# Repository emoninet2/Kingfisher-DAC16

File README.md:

# Kingfisher-DAC16
A 16 channel. 16-bit DAC board.

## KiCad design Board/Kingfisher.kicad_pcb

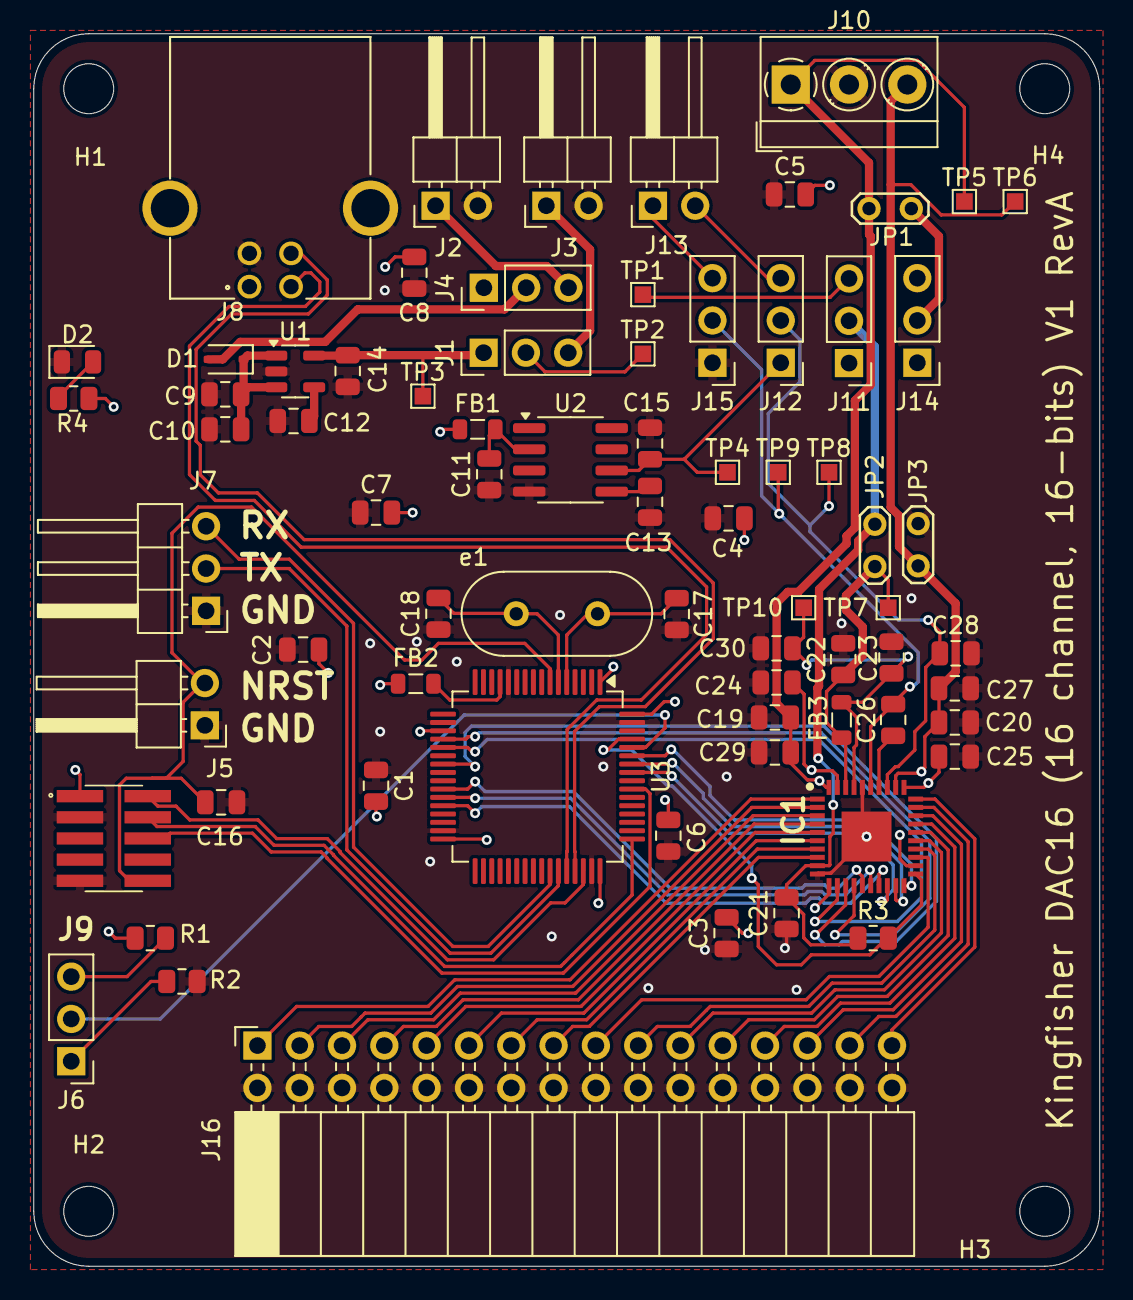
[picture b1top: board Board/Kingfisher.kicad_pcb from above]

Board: 4 copper layers, 64.0 x 74.0 mm, 77 parts (0 on the bottom side), 64 nets.

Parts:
C1, C2, C12: 10nF; C_0805_2012Metric
C3, C4, C5, C6, C10, C16, C19, C20, C21, C22, C23, C24, C25: 100nF; C_0805_2012Metric
C7, C9, C11, C13, C14, C30: 1uF; C_0805_2012Metric
C8, C15, C27, C29: 10uF; C_0805_2012Metric
C17, C18: 30pF; C_0805_2012Metric
C26: 330pF; C_0805_2012Metric
C28: 150nF; C_0805_2012Metric
D1: BAT60AE6327HTSA1; D_SOD-323
D2: LED; LED_0805_2012Metric
FB1, FB2, FB3: HZ0805E601R-10; L_0805_2012Metric
H1, H2, H3, H4: MountingHole; MountingHole_3mm
IC1: DAC81416RHAT; QFN50P600X600X100-41N-D
J1: SEL 3V3; PinHeader_1x03_P2.54mm_Vertical
J2: 5V EXT; PinHeader_1x02_P2.54mm_Horizontal
J3: 3V3 EXT; PinHeader_1x02_P2.54mm_Horizontal
J4: SEL 5V; PinHeader_1x03_P2.54mm_Vertical
J5: Conn_01x02_Male; PinHeader_1x02_P2.54mm_Horizontal
J6: Conn_01x03_Male; PinHeader_1x03_P2.54mm_Vertical
J7: UART; PinHeader_1x03_P2.54mm_Horizontal
J8: 292304-1; TE_292304-1
J9: FTSH-105-01-F-DV-K-P-TR; FTSH-105-XX-YYY-DV-K-P-TR
J10: Screw_Terminal_01x03; TerminalBlock_MetzConnect_Type059_RT06303HBWC_1x03_P3.50mm_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
J11, J14: DAC_VDD_SEL; PinHeader_1x03_P2.54mm_Vertical
J12, J15: DAC_REF_SEL; PinHeader_1x03_P2.54mm_Vertical
J13: DAC_EXT_REF; PinHeader_1x02_P2.54mm_Horizontal
J16: Conn_02x16_Counter_Clockwise; PinSocket_2x16_P2.54mm_Horizontal
JP1, JP2, JP3: Jumper_01x02_2.54mm; TestPoint_2Pads_Pitch2.54mm_Drill0.8mm
R1, R2, R3: 10K; R_0805_2012Metric
R4: 100; R_0805_2012Metric
TP1, TP2, TP3, TP4, TP5, TP6, TP7, TP8, TP9, TP10: TestPoint; TestPoint_Pad_1.0x1.0mm
U1: LDK130M33R; SOT-23-5
U2: REF5025AID; SOIC-8_3.9x4.9mm_P1.27mm
U3: STM32L476RGT6; LQFP-64_10x10mm_P0.5mm
e1: ECS-160-20-4X; Crystal_HC49-4H_Vertical

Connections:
3.3V_EXT: J1.3, J3.1
3.3V_REG: C14.2, J1.1, TP3.1, U1.5 (VOUT)
5V_EXT: J2.1, J4.3
+3V3: C1.2, C2.2, C3.2, C4.2, C5.2, C6.2, C7.2, C8.2, FB1.1, FB2.1, J1.2, J9.1, J11.1, J14.1, R1.1, R4.2, TP2.1, U3.1 (VBAT), U3.19 (VDD), U3.32 (VDD), U3.48 (VDDUSB), U3.64 (VDD)
+5V: D1.2 (A), J4.2, J11.3, J14.3, TP1.1
BOOT0: J6.2, U3.60 (PH3)
DAC_GNDREF: C26.1, IC1.35 (REFGND), J15.2, TP9.1
DAC_OUT_0: IC1.1 (OUT0), J16.1
DAC_OUT_1: IC1.2 (OUT1), J16.3
DAC_OUT_2: IC1.3 (OUT2), J16.5
DAC_OUT_3: IC1.4 (OUT3), J16.7
DAC_OUT_4: IC1.5 (OUT4), J16.9
DAC_OUT_5: IC1.6 (OUT5), J16.11
DAC_OUT_6: IC1.7 (OUT6), J16.13
DAC_OUT_7: IC1.8 (OUT7), J16.15
DAC_OUT_8: IC1.23 (OUT8), J16.17
DAC_OUT_9: IC1.24 (OUT9), J16.19
DAC_OUT_10: IC1.25 (OUT10), J16.21
DAC_OUT_11: IC1.26 (OUT11), J16.23
DAC_OUT_12: IC1.27 (OUT12), J16.25
DAC_OUT_13: IC1.28 (OUT13), J16.27
DAC_OUT_14: IC1.29 (OUT14), J16.29
DAC_OUT_15: IC1.30 (OUT15), J16.31
DAC_REF: C28.1, IC1.33 (REF), J12.2, TP8.1
DAC_SCLK: IC1.12 (SCLK), U3.21 (PA5)
DAC_SDI: IC1.13 (SDI), U3.23 (PA7)
DAC_TOGGLE0: IC1.15 (TOGGLE0), U3.26 (PB0)
DAC_TOGGLE1: IC1.16 (TOGGLE1), U3.27 (PB1)
DAC_TOGGLE2: IC1.17 (TOGGLE2), U3.28 (PB2)
DAC_VAA: C23.2, C30.2, FB3.2, IC1.37 (VAA), TP10.1
DAC_VCC: C19.2, C25.2, C29.2, IC1.31 (VCC_1), IC1.40 (VCC_2), J10.1, JP1.1 (A), TP5.1
DAC_VDD: C22.2, FB3.1, IC1.38 (VDD), JP2.2 (B), TP7.1
DAC_VIO: C21.2, IC1.9 (VIO), J11.2, JP2.1 (A), R3.1
DAC_VSS: C20.2, C24.2, C27.2, IC1.32 (VSS_1), IC1.39 (VSS_2), J10.3, JP3.1 (A), TP6.1
DAC_nALMOUT: IC1.21 (~ALMOUT), R3.2, U3.61 (PB8)
DAC_nCLR: IC1.20 (~CLR), U3.59 (PB7)
DAC_nCS: IC1.14 (~CS), U3.20 (PA4)
DAC_nLDAC: IC1.18 (~LDAC), U3.57 (PB5)
DAC_nRESET: IC1.19 (~RESET), U3.58 (PB6)
EXT_REF_2V5: J12.3, J13.2
GND: C1.1, C2.1, C3.1, C4.1, C5.1, C6.1, C7.1, C8.1, C9.1, C10.1, C11.1, C12.1, C13.1, C14.1, C15.1, C16.1, C17.1, C18.1, C19.1, C20.1, C21.1, C22.1, C23.1, C24.1, C25.1, C27.1, C28.2, C29.1, C30.1, D2.1 (K), IC1.10 (GND_1), IC1.36 (GND_2), IC1.41 (EPAD), J2.2, J3.2, J5.1, J7.1, J8.0 (SHEILD), J8.4 (GND), J9.3, J9.9, J10.2, J15.1, J16.2, J16.4, J16.6, J16.8, J16.10, J16.12, J16.14, J16.16, J16.18, J16.20, J16.22, J16.24, J16.26, J16.28, J16.30, J16.32, JP3.2 (B), R2.2, U1.2 (GND), U2.4 (GND), U3.12 (VSSA), U3.18 (VSS), U3.31 (VSS), U3.47 (VSS), U3.63 (VSS)
JTCK_SWCLK: J9.4, U3.49 (PA14)
JTDO_SWO: J9.6, U3.55 (PB3)
JTMS_SWDIO: J9.2, U3.46 (PA13)
NRST: C16.2, J5.2, J9.10, U3.7 (NRST)
unnamed: C9.2, C10.2, D1.1 (K), U1.1 (VIN), U1.3 (INH)
unnamed: D2.2 (A), R4.1
unnamed: C26.2, IC1.34 (REFCMP)
unnamed: J6.1, R2.1
unnamed: J6.3, R1.2
unnamed: J13.1, J15.3
unnamed: J14.2, JP1.2 (B)
unnamed: C12.2, U1.4 (BYP)
unnamed: C13.2, U2.5 (Trim/NR)
unnamed: C11.2, FB1.2, U2.2 (Vin)
unnamed: C17.2, U3.5 (PH0), e1.1
unnamed: C18.2, U3.6 (PH1), e1.2
unnamed: FB2.2, U3.13 (VDDA)
REF_2V5: C15.2, J12.1, TP4.1, U2.6 (Vout)
UART_RX: J7.3, U3.42 (PA9)
UART_TX: J7.2, U3.43 (PA10)
USB_OTG_FS_D+: J8.3 (D+), U3.45 (PA12)
USB_OTG_FS_D-: J8.2 (D-), U3.44 (PA11)
USB_VBUS: J4.1, J8.1 (VBUS)

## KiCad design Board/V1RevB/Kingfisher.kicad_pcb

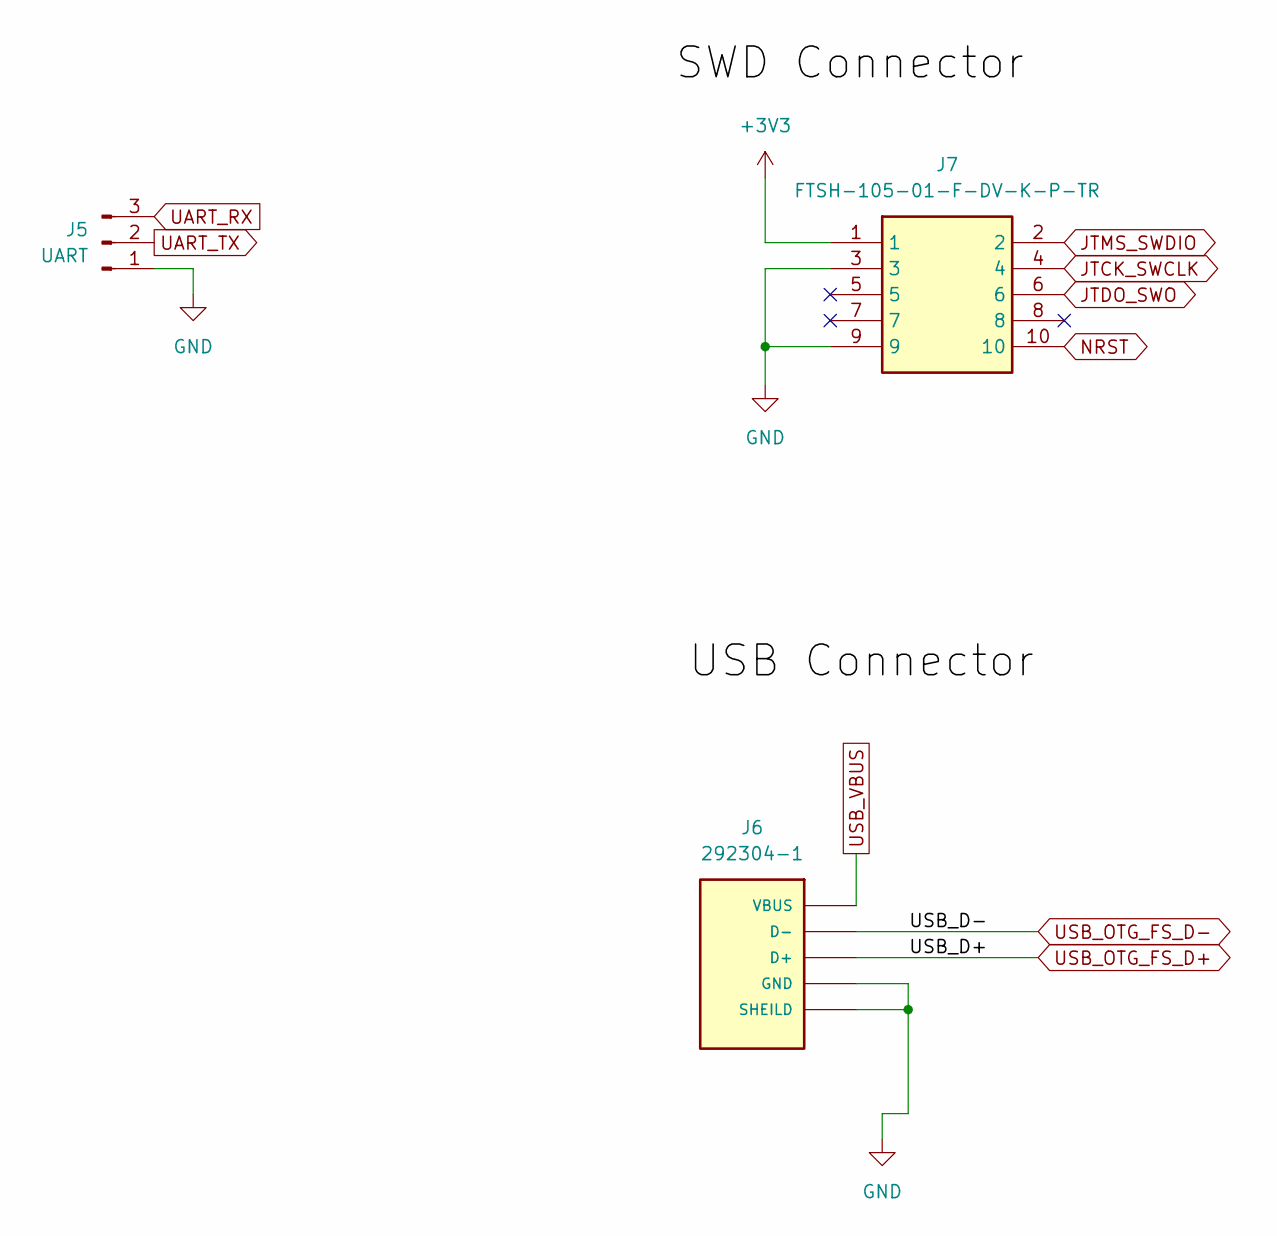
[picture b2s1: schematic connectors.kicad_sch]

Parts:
J5: UART; PinHeader_1x03_P2.54mm_Horizontal; Manufacturer_Part_Number TSW-103-14-TM-S; Farnell 1593427
J6: 292304-1; TE_292304-1; Manufacturer_Part_Number 292304-1; LCSC C86462
J7: FTSH-105-01-F-DV-K-P-TR; FTSH-105-XX-YYY-DV-K-P-TR; Mouser Part Number FTSH-105-01-F-DV-K-P-TR

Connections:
+3V3: J7.1; also elsewhere on the board
GND: J5.1, J6.0 (SHEILD), J6.4 (GND), J7.3, J7.9; also elsewhere on the board
JTCK_SWCLK: J7.4; also elsewhere on the board
JTDO_SWO: J7.6; also elsewhere on the board
JTMS_SWDIO: J7.2; also elsewhere on the board
NRST: J7.10; also elsewhere on the board
UART_RX: J5.3; also elsewhere on the board
UART_TX: J5.2; also elsewhere on the board
USB_OTG_FS_D+: J6.3 (D+); also elsewhere on the board
USB_OTG_FS_D-: J6.2 (D-); also elsewhere on the board
USB_VBUS: J6.1 (VBUS); also elsewhere on the board

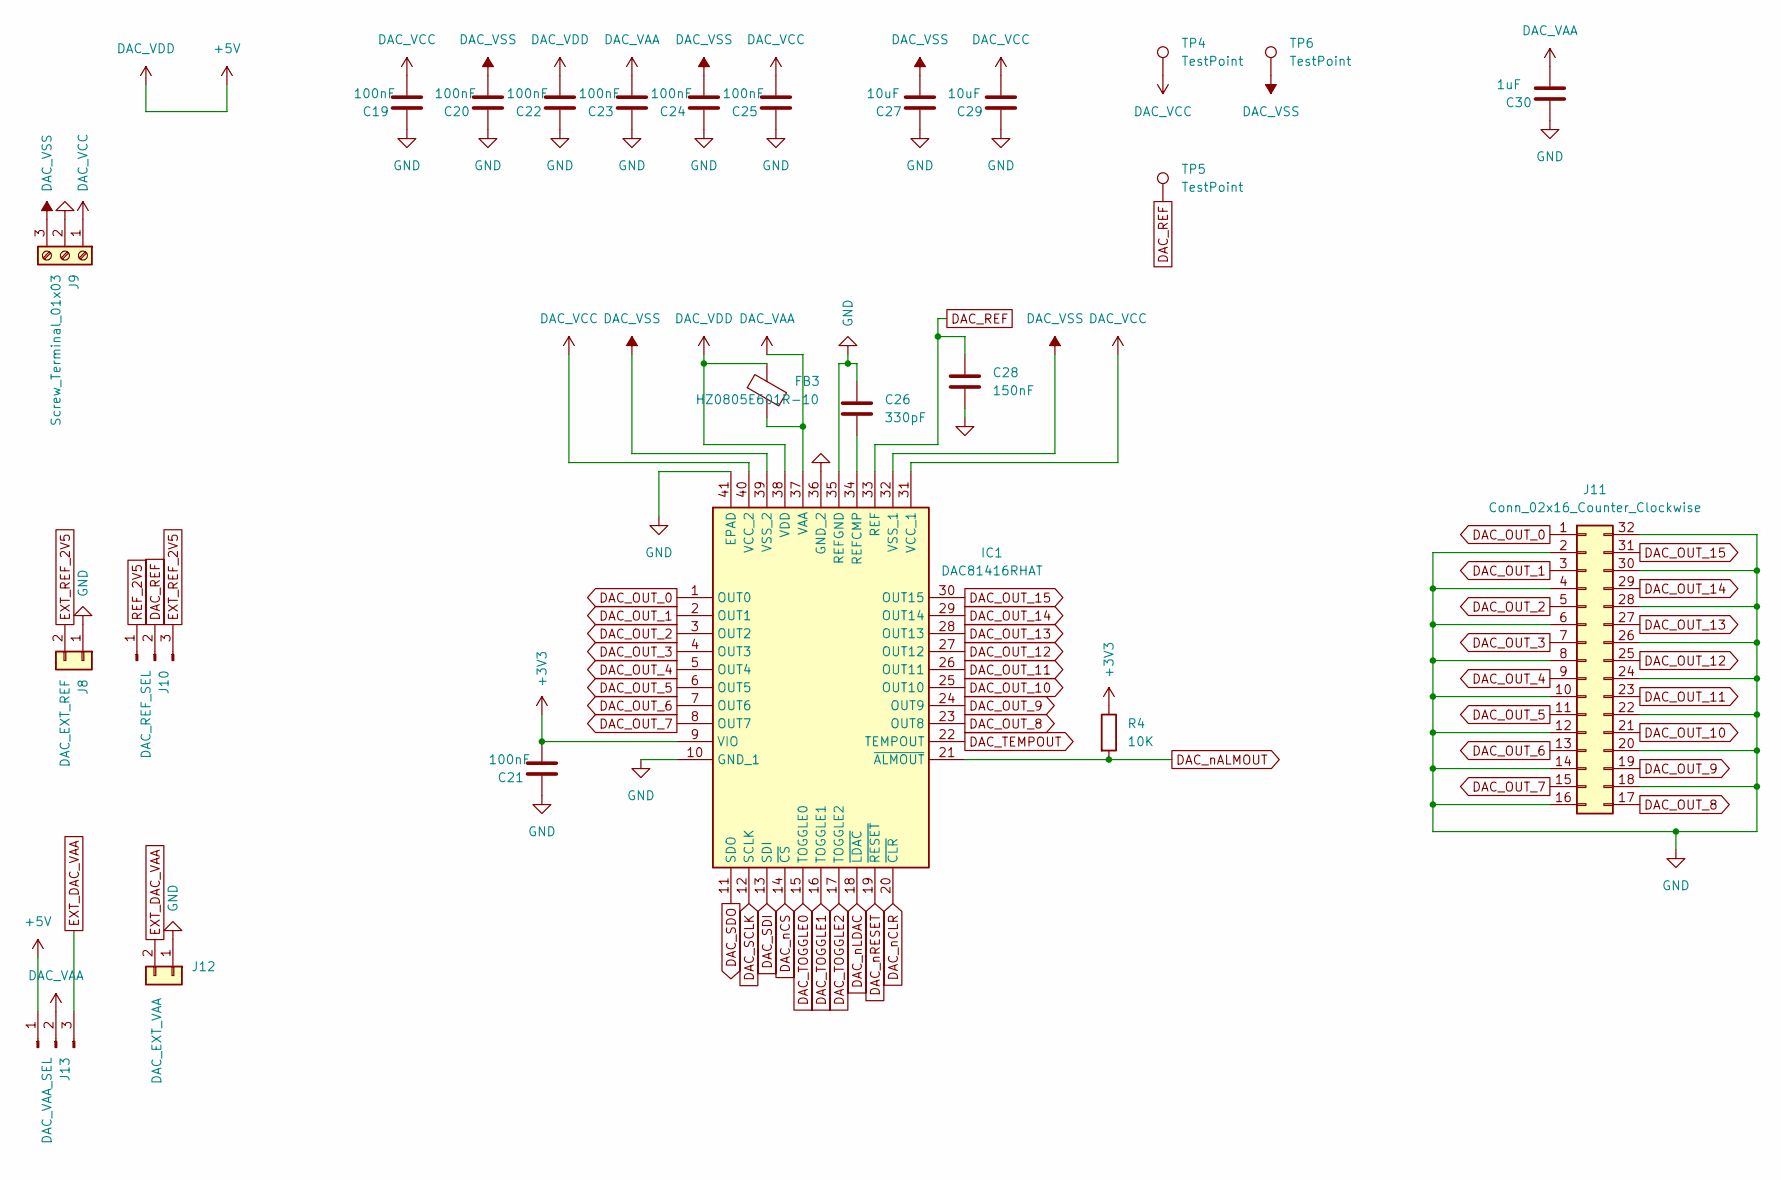
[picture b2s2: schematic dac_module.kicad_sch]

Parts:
C19, C20, C21, C22, C23, C24, C25: 100nF; C_0805_2012Metric; Manufacturer_Part_Number CL21B104KBCNNNC; LCSC C1711
C26: 330pF; C_0805_2012Metric; Mouser Part Number 08052C331KAT2A; Digi-Key Part Number 478-KGM21NR72D331KTCT-ND
C27, C29: 10uF; C_0805_2012Metric; Manufacturer_Part_Number CL21A106KOQNNNG; LCSC C307520
C28: 150nF; C_0805_2012Metric; Mouser Part Number C0805C154K5RACAUTO; Digi-Key Part Number 399-15888-1-ND
C30: 1uF; C_0805_2012Metric; Manufacturer_Part_Number CL21A105KBCLNNC; LCSC C318694
FB3: HZ0805E601R-10; L_0805_2012Metric; Manufacturer_Part_Number HZ0805E601R-10; Digi-Key Part Number 240-2399-1-ND
IC1: DAC81416RHAT; QFN50P600X600X100-41N-D; Mouser Part Number DAC81416RHAT
J8: DAC_EXT_REF; PinHeader_1x02_P2.54mm_Horizontal; Mouser Part Number MC34745; Farnell 1593426
J9: Screw_Terminal_01x03; TerminalBlock_MetzConnect_Type059_RT06303HBWC_1x03_P3.50mm_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; Mouser Part Number METZ CONNECT; Farnell 31059103
J10: DAC_REF_SEL; PinHeader_1x03_P2.54mm_Vertical; Manufacturer_Part_Number TSW-103-14-TM-S; Farnell 3398484
J11: Conn_02x16_Counter_Clockwise; PinSocket_2x16_P2.54mm_Horizontal; Mouser Part Number SSW-108-02-F-D-RA; Farnell 3661253
J12: DAC_EXT_VAA; PinHeader_1x02_P2.54mm_Horizontal; Mouser Part Number MC34745; Farnell 1593426
J13: DAC_VAA_SEL; PinHeader_1x03_P2.54mm_Vertical; Manufacturer_Part_Number TSW-103-14-TM-S; Farnell 3398484
R4: 10K; R_0805_2012Metric; Mouser Part Number CRCW080510K0JNEAIF; Farnell 1739242
TP4, TP5, TP6: TestPoint; TestPoint_Pad_1.0x1.0mm

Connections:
+3V3: C21.2, IC1.9 (VIO), R4.1; also elsewhere on the board
+5V: C22.2, FB3.1, IC1.38 (VDD), J13.1; also elsewhere on the board
DAC_OUT_0: IC1.1 (OUT0), J11.1
DAC_OUT_1: IC1.2 (OUT1), J11.3
DAC_OUT_2: IC1.3 (OUT2), J11.5
DAC_OUT_3: IC1.4 (OUT3), J11.7
DAC_OUT_4: IC1.5 (OUT4), J11.9
DAC_OUT_5: IC1.6 (OUT5), J11.11
DAC_OUT_6: IC1.7 (OUT6), J11.13
DAC_OUT_7: IC1.8 (OUT7), J11.15
DAC_OUT_8: IC1.23 (OUT8), J11.17
DAC_OUT_9: IC1.24 (OUT9), J11.19
DAC_OUT_10: IC1.25 (OUT10), J11.21
DAC_OUT_11: IC1.26 (OUT11), J11.23
DAC_OUT_12: IC1.27 (OUT12), J11.25
DAC_OUT_13: IC1.28 (OUT13), J11.27
DAC_OUT_14: IC1.29 (OUT14), J11.29
DAC_OUT_15: IC1.30 (OUT15), J11.31
DAC_REF: C28.1, IC1.33 (REF), J10.2, TP5.1
DAC_SCLK: IC1.12 (SCLK); also elsewhere on the board
DAC_SDI: IC1.13 (SDI); also elsewhere on the board
DAC_SDO: IC1.11 (SDO); also elsewhere on the board
DAC_TEMPOUT: IC1.22 (TEMPOUT)
DAC_TOGGLE0: IC1.15 (TOGGLE0); also elsewhere on the board
DAC_TOGGLE1: IC1.16 (TOGGLE1); also elsewhere on the board
DAC_TOGGLE2: IC1.17 (TOGGLE2); also elsewhere on the board
DAC_VAA: C23.2, C30.2, FB3.2, IC1.37 (VAA), J13.2
DAC_VCC: C19.2, C25.2, C29.2, IC1.31 (VCC_1), IC1.40 (VCC_2), J9.1, TP4.1
DAC_VSS: C20.2, C24.2, C27.2, IC1.32 (VSS_1), IC1.39 (VSS_2), J9.3, TP6.1
DAC_nALMOUT: IC1.21 (~ALMOUT), R4.2; also elsewhere on the board
DAC_nCLR: IC1.20 (~CLR); also elsewhere on the board
DAC_nCS: IC1.14 (~CS); also elsewhere on the board
DAC_nLDAC: IC1.18 (~LDAC); also elsewhere on the board
DAC_nRESET: IC1.19 (~RESET); also elsewhere on the board
EXT_DAC_VAA: J12.2, J13.3
EXT_REF_2V5: J8.2, J10.3
GND: C19.1, C20.1, C21.1, C22.1, C23.1, C24.1, C25.1, C26.1, C27.1, C28.2, C29.1, C30.1, IC1.10 (GND_1), IC1.35 (REFGND), IC1.36 (GND_2), IC1.41 (EPAD), J8.1, J9.2, J11.2, J11.4, J11.6, J11.8, J11.10, J11.12, J11.14, J11.16, J11.18, J11.20, J11.22, J11.24, J11.26, J11.28, J11.30, J11.32, J12.1; also elsewhere on the board
unnamed: C26.2, IC1.34 (REFCMP)
REF_2V5: J10.1; also elsewhere on the board

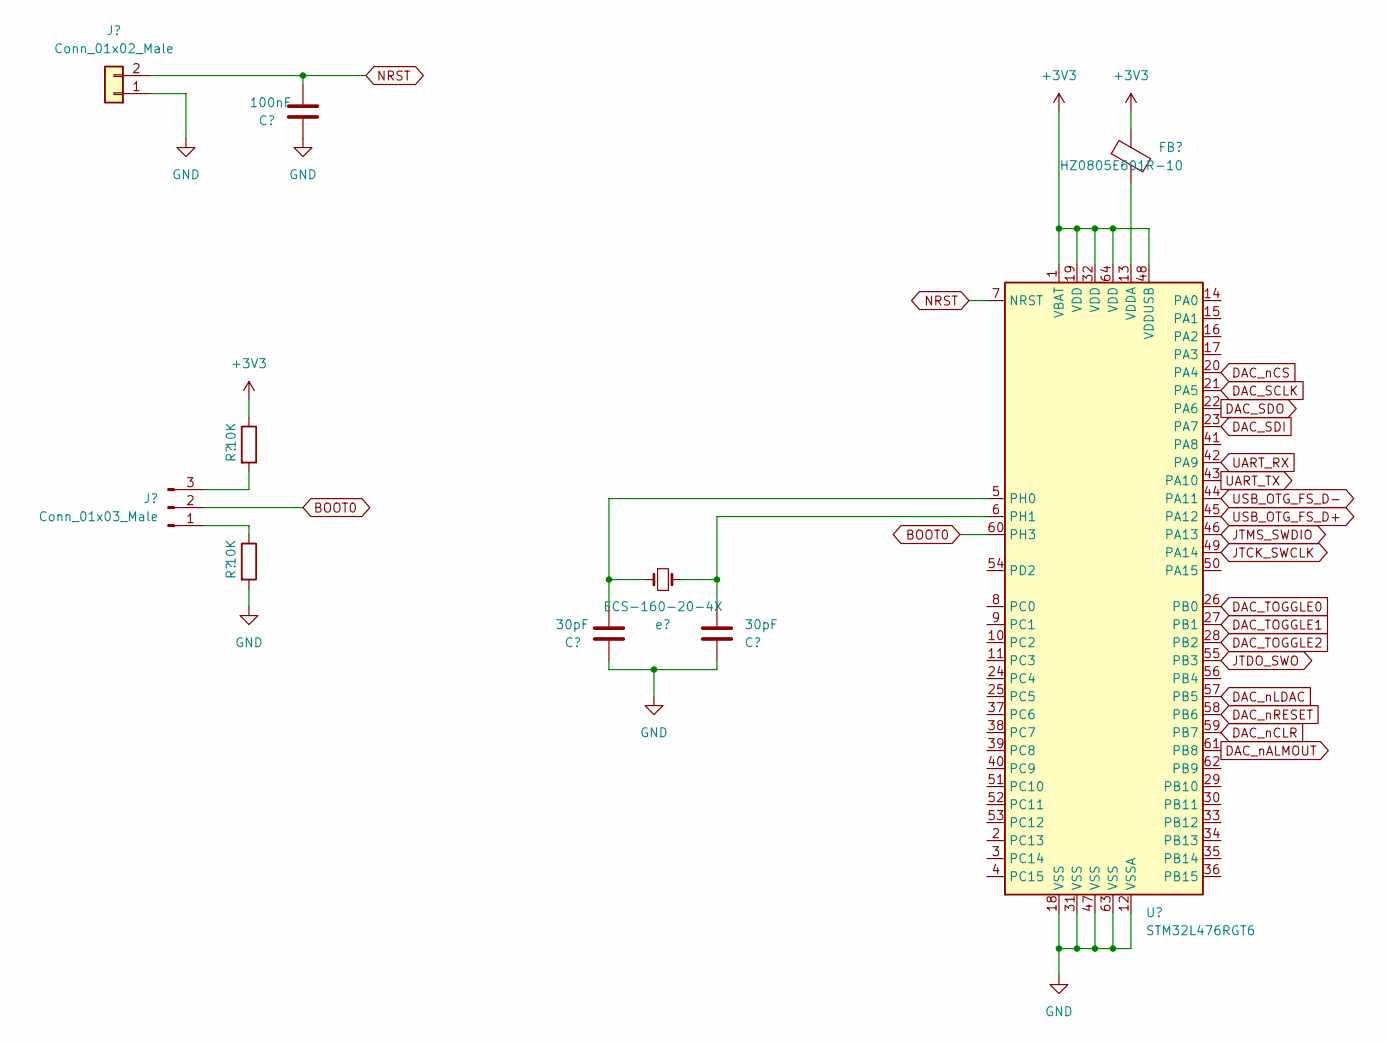
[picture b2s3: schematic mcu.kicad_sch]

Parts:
C16: 100nF; C_0805_2012Metric; Manufacturer_Part_Number CL21B104KBCNNNC; LCSC C1711
C17, C18: 30pF; C_0805_2012Metric; Manufacturer_Part_Number CL21C200JBANNNC; LCSC C1798
FB2: HZ0805E601R-10; L_0805_2012Metric; Manufacturer_Part_Number HZ0805E601R-10; Digi-Key Part Number 240-2399-1-ND
J3: Conn_01x02_Male; PinHeader_1x02_P2.54mm_Horizontal; Manufacturer_Part_Number TSW-102-14-TM-S; Farnell MC34745
J4: Conn_01x03_Male; PinHeader_1x03_P2.54mm_Vertical; Manufacturer_Part_Number TSW-103-14-TM-S; Farnell 3398484
R2, R3: 10K; R_0805_2012Metric; Manufacturer_Part_Number ERA-6AEB103V; Farnell 1739242
U3: STM32L476RGT6; LQFP-64_10x10mm_P0.5mm; Manufacturer_Part_Number STM32L476RGT6; LCSC C74797
e1: ECS-160-20-4X; Crystal_HC49-4H_Vertical; Manufacturer_Part_Number 9B-16.000MAAE-B; LCSC C2636524

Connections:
+3V3: FB2.1, R2.1, U3.1 (VBAT), U3.19 (VDD), U3.32 (VDD), U3.48 (VDDUSB), U3.64 (VDD); also elsewhere on the board
BOOT0: J4.2, U3.60 (PH3)
DAC_SCLK: U3.21 (PA5); also elsewhere on the board
DAC_SDI: U3.23 (PA7); also elsewhere on the board
DAC_SDO: U3.22 (PA6); also elsewhere on the board
DAC_TOGGLE0: U3.26 (PB0); also elsewhere on the board
DAC_TOGGLE1: U3.27 (PB1); also elsewhere on the board
DAC_TOGGLE2: U3.28 (PB2); also elsewhere on the board
DAC_nALMOUT: U3.61 (PB8); also elsewhere on the board
DAC_nCLR: U3.59 (PB7); also elsewhere on the board
DAC_nCS: U3.20 (PA4); also elsewhere on the board
DAC_nLDAC: U3.57 (PB5); also elsewhere on the board
DAC_nRESET: U3.58 (PB6); also elsewhere on the board
GND: C16.1, C17.1, C18.1, J3.1, R3.2, U3.12 (VSSA), U3.18 (VSS), U3.31 (VSS), U3.47 (VSS), U3.63 (VSS); also elsewhere on the board
JTCK_SWCLK: U3.49 (PA14); also elsewhere on the board
JTDO_SWO: U3.55 (PB3); also elsewhere on the board
JTMS_SWDIO: U3.46 (PA13); also elsewhere on the board
NRST: C16.2, J3.2, U3.7 (NRST); also elsewhere on the board
unnamed: J4.1, R3.1
unnamed: J4.3, R2.2
unnamed: C17.2, U3.5 (PH0), e1.1
unnamed: C18.2, U3.6 (PH1), e1.2
unnamed: FB2.2, U3.13 (VDDA)
UART_RX: U3.42 (PA9); also elsewhere on the board
UART_TX: U3.43 (PA10); also elsewhere on the board
USB_OTG_FS_D+: U3.45 (PA12); also elsewhere on the board
USB_OTG_FS_D-: U3.44 (PA11); also elsewhere on the board

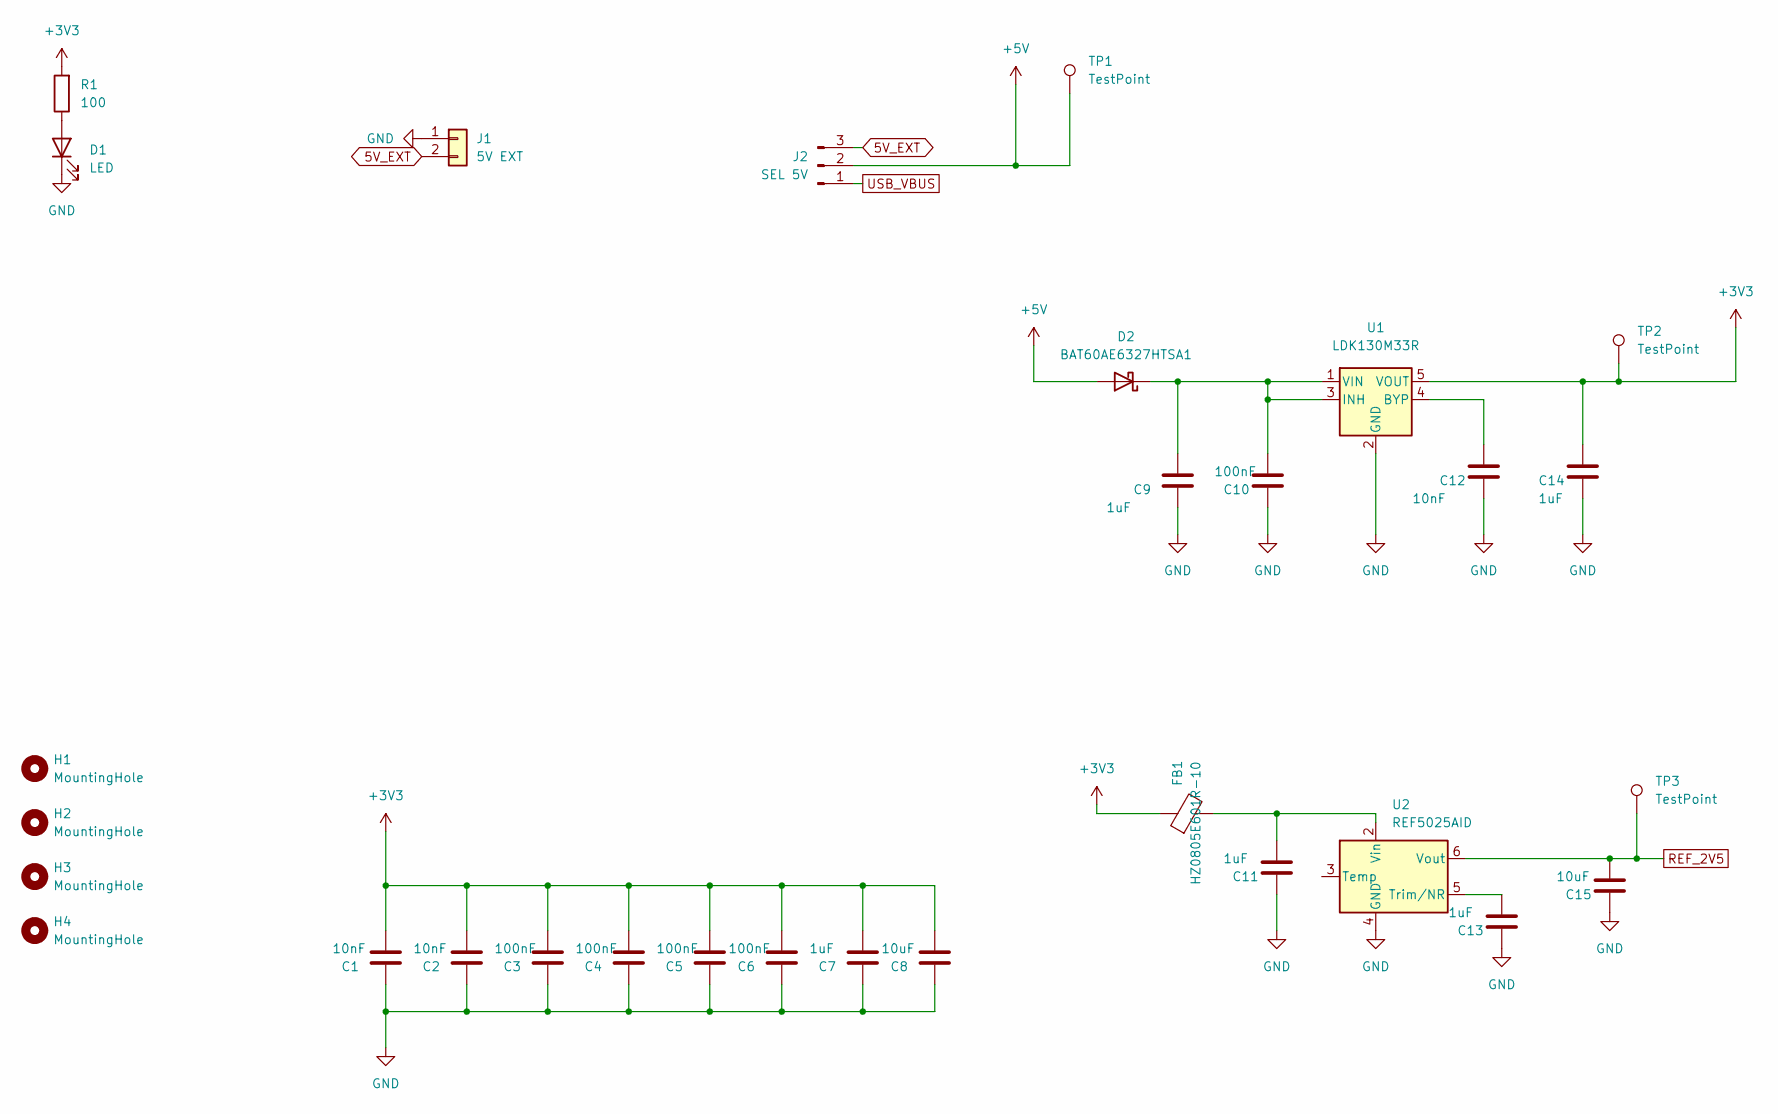
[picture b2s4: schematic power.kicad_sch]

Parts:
C1, C2, C12: 10nF; C_0805_2012Metric; Manufacturer_Part_Number CL21B103KBANNNC; LCSC C1710
C3, C4, C5, C6, C10: 100nF; C_0805_2012Metric; Manufacturer_Part_Number CL21B104KBCNNNC; LCSC C1711
C7, C9, C11, C13, C14: 1uF; C_0805_2012Metric; Manufacturer_Part_Number CL21A105KBCLNNC; LCSC C318694
C8, C15: 10uF; C_0805_2012Metric; Manufacturer_Part_Number CL21A106KOQNNNG; LCSC C307520
D1: LED; LED_0805_2012Metric; Manufacturer_Part_Number LTST-C191KRKT; LCSC C125099
D2: BAT60AE6327HTSA1; D_SOD-323; Manufacturer_Part_Number BAT60AE6327HTSA1; Digi-Key Part Number BAT60AE6327HTSA1CT-ND
FB1: HZ0805E601R-10; L_0805_2012Metric; Manufacturer_Part_Number HZ0805E601R-10; Digi-Key Part Number 240-2399-1-ND
H1, H2, H3, H4: MountingHole; MountingHole_3mm
J1: 5V EXT; PinHeader_1x02_P2.54mm_Horizontal; Manufacturer_Part_Number TSW-102-14-TM-S; Farnell 1593426
J2: SEL 5V; PinHeader_1x03_P2.54mm_Vertical; Manufacturer_Part_Number TSW-103-14-TM-S; Farnell 3398484
R1: 100; R_0805_2012Metric; Manufacturer_Part_Number AC0805FR-07100RL; Farnell 1652906
TP1, TP2, TP3: TestPoint; TestPoint_Pad_1.0x1.0mm
U1: LDK130M33R; SOT-23-5; Manufacturer_Part_Number LD3985M33R; LCSC C46243
U2: REF5025AID; SOIC-8_3.9x4.9mm_P1.27mm; Mouser Part Number REF5025AID; Digi-Key Part Number 296-22203-5-ND

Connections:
5V_EXT: J1.2, J2.3
+3V3: C1.2, C2.2, C3.2, C4.2, C5.2, C6.2, C7.2, C8.2, C14.2, FB1.1, R1.2, TP2.1, U1.5 (VOUT); also elsewhere on the board
+5V: D2.2 (A), J2.2, TP1.1; also elsewhere on the board
GND: C1.1, C2.1, C3.1, C4.1, C5.1, C6.1, C7.1, C8.1, C9.1, C10.1, C11.1, C12.1, C13.1, C14.1, C15.1, D1.1 (K), J1.1, U1.2 (GND), U2.4 (GND); also elsewhere on the board
unnamed: D1.2 (A), R1.1
unnamed: C9.2, C10.2, D2.1 (K), U1.1 (VIN), U1.3 (INH)
unnamed: C12.2, U1.4 (BYP)
unnamed: C13.2, U2.5 (Trim/NR)
unnamed: C11.2, FB1.2, U2.2 (Vin)
REF_2V5: C15.2, TP3.1, U2.6 (Vout); also elsewhere on the board
USB_VBUS: J2.1; also elsewhere on the board

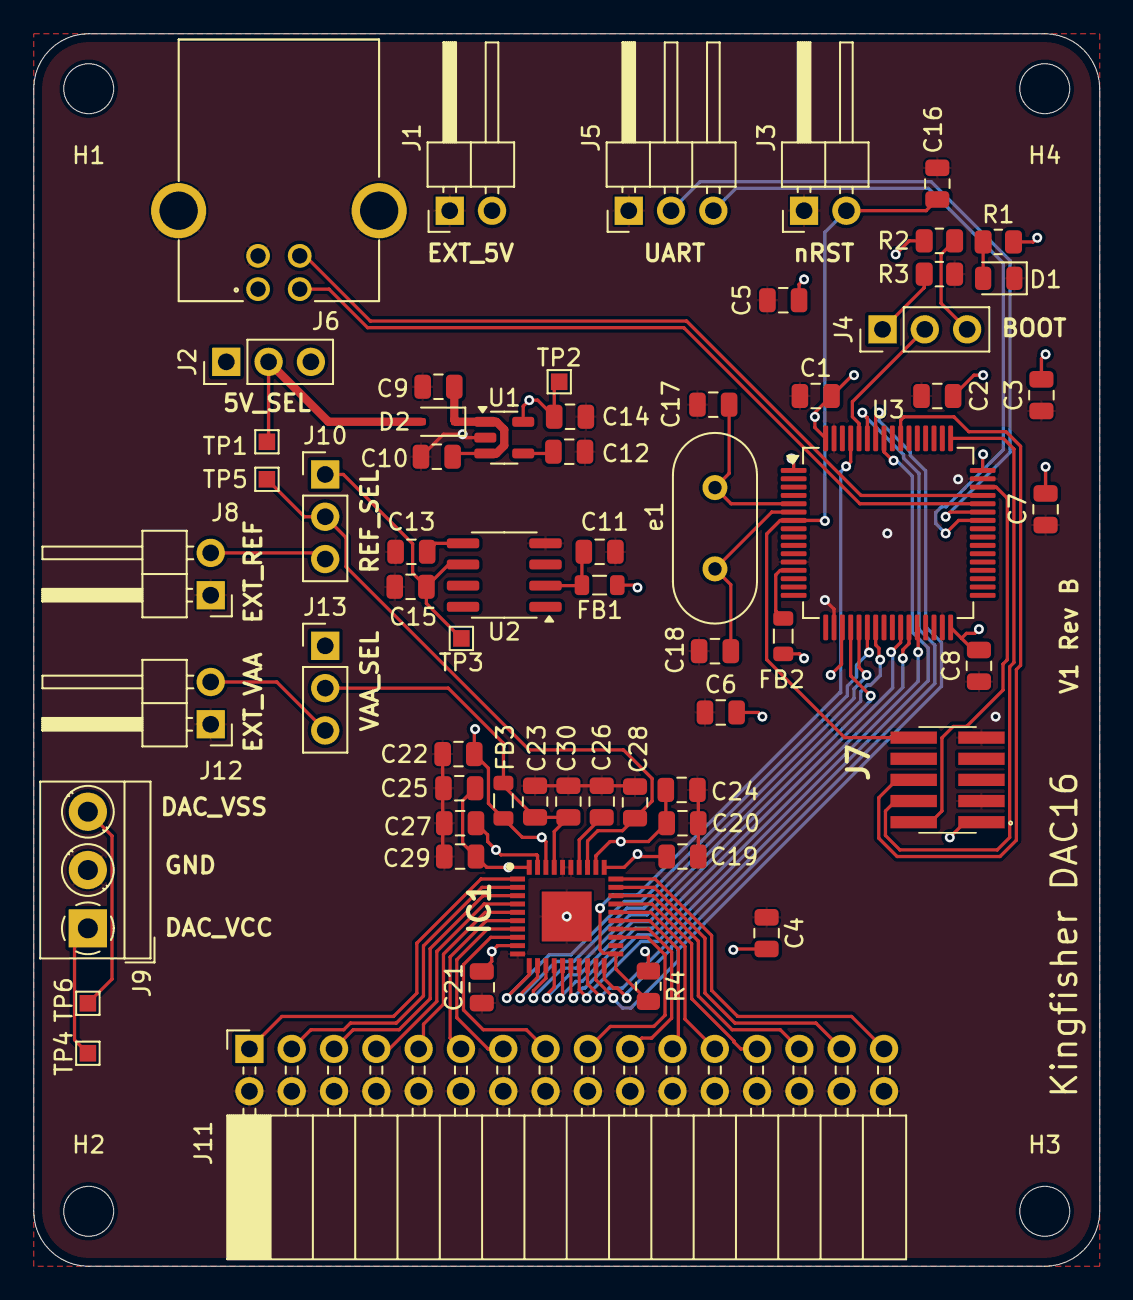
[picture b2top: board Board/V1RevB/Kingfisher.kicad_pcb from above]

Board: 4 copper layers, 64.0 x 74.0 mm, 67 parts (0 on the bottom side), 59 nets.

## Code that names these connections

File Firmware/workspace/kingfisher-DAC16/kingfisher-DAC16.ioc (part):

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Mcu.Name=STM32L476R(C-E-G)Tx
Mcu.Package=LQFP64
Mcu.UserName=STM32L476RGTx
PA10.Mode=Asynchronous
PA10.Signal=USART1_RX
PA11.Mode=Device_Only
PA11.Signal=USB_OTG_FS_DM
PA12.Mode=Device_Only
PA12.Signal=USB_OTG_FS_DP
PA13\ (JTMS-SWDIO).Mode=Trace_Asynchronous_SW
PA13\ (JTMS-SWDIO).Signal=SYS_JTMS-SWDIO
PA14\ (JTCK-SWCLK).Mode=Trace_Asynchronous_SW
PA14\ (JTCK-SWCLK).Signal=SYS_JTCK-SWCLK
PA4.GPIOParameters=GPIO_Label
PA4.GPIO_Label=DAC_nCS
PA4.Signal=GPIO_Output
PA5.Mode=Full_Duplex_Master
PA5.Signal=SPI1_SCK
PA6.Mode=Full_Duplex_Master
PA6.Signal=SPI1_MISO
PA7.Mode=Full_Duplex_Master
PA7.Signal=SPI1_MOSI
PA9.Mode=Asynchronous
PA9.Signal=USART1_TX
PB0.GPIOParameters=GPIO_Label
PB0.GPIO_Label=DAC_TOGGLE0
PB0.Signal=GPIO_Output
PB1.GPIOParameters=GPIO_Label
PB1.GPIO_Label=DAC_TOGGLE1
PB1.Signal=GPIO_Output
PB2.GPIOParameters=GPIO_Label
PB2.GPIO_Label=DAC_TOGGLE2
PB2.Signal=GPIO_Output
PB3\ (JTDO-TRACESWO).Mode=Trace_Asynchronous_SW
PB3\ (JTDO-TRACESWO).Signal=SYS_JTDO-SWO
PB5.GPIOParameters=GPIO_Label
PB5.GPIO_Label=DAC_nLDAC
PB5.Signal=GPIO_Output
PB6.GPIOParameters=GPIO_Label
PB6.GPIO_Label=DAC_nRESET
PB6.Signal=GPIO_Output
PB7.GPIOParameters=GPIO_Label
PB7.GPIO_Label=DAC_nCLR
PB7.Signal=GPIO_Output
PB8.GPIOParameters=GPIO_Label
PB8.GPIO_Label=DAC_nALMOUT
PB8.Signal=GPXTI8
PH0-OSC_IN\ (PH0).Mode=HSE-External-Oscillator
PH0-OSC_IN\ (PH0).Signal=RCC_OSC_IN
PH1-OSC_OUT\ (PH1).Mode=HSE-External-Oscillator
PH1-OSC_OUT\ (PH1).Signal=RCC_OSC_OUT
RCC.HSE_VALUE=16000000
RCC.SYSCLKFreq_VALUE=80000000
RCC.SYSCLKSource=RCC_SYSCLKSOURCE_PLLCLK
board=custom

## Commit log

2024-09-12 added exisitng project contents
2024-10-19 added draft for V1 Rev B
2024-10-28 renamed project name in firmware workspace
2024-10-29 updated driver
2024-10-31 tested dac register read and write with crc
2024-11-22 updated firmware to use SLIP. completed python driver and tested
2026-04-10 created install file for python to setup venv and install required packages
2026-04-10 fixed crc usage
2026-04-10 added extended command for hardware reset
2026-04-10 edited example with some explaination for simple use
